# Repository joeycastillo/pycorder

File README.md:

The PyCorder
============

A credit-card-sized, SAM D51-based gadget for sensing, storing and showing data.

PCB (new link soon)) | [BOM](https://octopart.com/bom-tool/ggGZZjZ3) | [UPDATES](https://twitter.com/josecastillo)

Features
--------

* A distinctly crisp and impressively low power 240x400 Sharp Memory Display
* A SAMD51G19 microcontroller, with plenty of room for [CircuitPython](https://circuitpython.org/)!
* 4 megabyte QSPI Flash; plenty of space for code, fonts and images
* Two buttons and a five-way joystick for user input
* Built-in battery charging, and room for a [350 mAh battery](https://www.adafruit.com/product/4237)
* One STEMMA port with current limiting and voltage protection
* One STEMMA-QT port for plugging in [STEMMA-QT compatible boards](https://www.adafruit.com/category/1018)
* One 9-pin connector, compatible with a veritable menagerie of [Sensor Cap](https://github.com/joeycastillo/Sensor-Cap/tree/main/PCB/Sensor%20Boards) sensor boards
* Enable switch for cutting power to the device
* One amber LED for charge state and one red LED for general purpose blinking

Building your own PyCorder
--------------------------

You will need to order the PCB's from someplace like OSH Park (I recommend getting it in After Dark), and purchase all the parts on the [PyCorder Bill of Materials](https://octopart.com/bom-tool/ggGZZjZ3).

The board is hand-solderable, but a word of warning: **this is a relatively advanced build**. The SAM D51 microcontroller is a QFN part, which is best soldered with a hot air reflow station. Aside from that, almost all of the passive components are 0603 in size, which is at the limit of hand-solderability for many folks. A [fine tip](https://www.adafruit.com/product/1249) for your soldering iron is a must, and a [syringe of flux](https://www.adafruit.com/product/2667) couldn't hurt.

Pin definitions
---------------

Unlike a Metro or even a Feather, the PyCorder doesn't have a whole heap of GPIO pins. Having said that, I made sure to choose the pins with the most diverse set of features, opening the door to a whole lot of possibilities.

The **STEMMA port** is arguably one of the most powerful pins on the microcontroller. You can use it as a 10-bit true analog output, analog input, digital in/out or PWM. Access it in CircuitPython as `board.STEMMA`.

The **STEMMA-QT port** gives access to the board's I²C pins. Get at the I²C bus with `board.I2C()`, or the pins with `board.SDA` / `board.SCL`.

The **9-pin connector** can be used in a lot of different ways. From the top of the connector (which is pin 9):

* Pin 9, or `board.A0`, is the SAMD51's other DAC channel. Use this as an analog output, analog input or digital in/out.
* Pins 8 and 7 are the same I²C pins as the STEMMA-QT port; all I²C devices share the `board.I2C()` bus.
* Pin 6 has two names: `board.A1` and `board.SCK`. It can act as an analog input, PWM or digital in/out. In addition, it can act as the SCK pin for an SPI device on the other end of the 9-pin cable.
* Pin 5 (`board.A2` / `board.MOSI`) can act as an analog input, PWM, digital in/out, and the Main Out / Secondary In for an SPI device.
* Pin 4 (`board.D0` / `board.CS`) cannot support analog input, but you do get PWM and digital in/out. Can act as chip select for an SPI device.
* Pin 3 (`board.D1` / `board.MISO`) is PWM or digital in/out. Can act as the Main In / Secondary Out for an SPI device.
* Pin 2 is ground. 
* Pin 1 is a regulated 3.3 volt output from the on-board regulator.

The board has a **dual-output votage regulator** that can gate power to these three ports separately from the rest of the device. The enable pin for the main regulator output is, of course, tied to the on/off switch and pulled up by default. The second enable pin is tied to CircuitPython's `board.EN2`, and it is *pulled down by default*. This means that to power any device plugged in to these ports, you must do something like this first: 

```
en2 = DigitalInOut(board.EN2)
en2.switch_to_output()
en2.value = True
```

The LED is accessible at `board.LED`; you can output a digital signal to turn it on and off, or fade it with PWM.

Finally: the button inputs. These are easy: they're all active low and tied directly to pins on the SAMD51 (so you should enable internal pull-up resistors to use them). The rundown: 

* The button on the left side of the board is `board.PREVIOUS`
* The button on the right side is `board.NEXT`
* The four cardinal directions of the joystick map to `board.UP`, `board.DOWN`, `board.LEFT`, and `board.RIGHT`.
* You can press in on the joystick as a 'select' type action; detect this action on the `board.CENTER` pin.

Burning the bootloader
----------------------

You will burn the bootloader over the SWD interface. These pins are available as exposed test points on the right side of the back of the board. To connect to them, you can solder directly to the pads, or use pogo pins; they are 0.1 inch pitch, so you can make a compatible cable using [a 5x1 wire housing](https://www.adafruit.com/product/3145), [raw jumper wires](https://www.adafruit.com/product/3633) and [some pogo pins](https://www.adafruit.com/product/2429).

For convenience, a prebuilt bootloader is available in this repository. You can burn the bootloader using any SWD debugging tool like a J-Link or Atmel-ICE, but you can also use an [Adafruit Trinket M0](https://www.adafruit.com/product/3500) or [PyRuler](https://www.adafruit.com/product/4319) and the [Adafruit_DAP](https://github.com/adafruit/Adafruit_DAP) library.

You can also build the bootloader from scratch by copying the `bootloader/pycorder_m4` directory to the `boards` directory of [uf2-samdx1](https://github.com/adafruit/uf2-samdx1) and typing `make BOARD=pycorder_m4`.

CircuitPython on the PyCorder
-----------------------------

A CircuitPython UF2 is not included in this repository, because it's probably better to build your own with the latest greatest features. To get set up, follow the instructions in [Adafruit's guide to building CircuitPython](https://learn.adafruit.com/building-circuitpython?view=all); then copy the `circuitpython/pycorder_m4` directory to the CircuitPython repository's `ports/atmel-samd/boards` directory. 

Navigate to the `ports/atmel-samd` folder in your terminal and type `make BOARD=pycorder_m4`. This will generate a UF2 that you can drag to the PYCOBOOT drive.

Note that the CircuitPython build does not currently drive the display by default. Whether you intend to display console output or your own UI, you will have to paste some code like this at the beginning of your `code.py` to get the display working:

```
import busio
import framebufferio
import sharpdisplay
displayio.release_displays()
bus = busio.SPI(board.DISPLAY_CLOCK, MOSI=board.DISPLAY_DATA)
framebuffer = sharpdisplay.SharpMemoryFramebuffer(bus, board.DISPLAY_CS, 400, 240)
display = framebufferio.FramebufferDisplay(framebuffer, auto_refresh = True, rotation=270)
```

At this point you can add `display.show(None)` to display the CircuitPython console, or if you wish to show a displayio Group, `display.show(your_group)`.

Two final notes on the display: first, per the data sheet, the display requires a constant ~1Hz pulse on its EXTCOMIN pin. This reverses the polarity of the LCD, and is necessary for the display's long term stability. The CircuitPython board definition sets this pulse up as a PWM in its `board_init` function. If you wanted to do something like an Arduino core for it, you would be responsible for zatzing the display roughly once a second. EXTCOMIN is tied to the SAMD51's pin PA01, and the TC2 peripheral is ideal for generating this signal.

Second: the display only turns on when its DISP pin is pulled high, but the PyCorder connects it via a pull-down resistor so that the display defaults to an off state. This is intentional: the goal is to prevent the screen from turning on in the absence of the EXTCOMIN signal and degrading. DISP is tied to the SAMD51's pin PA00, and the `board_init` function pulls it high right after setting up the 1Hz pulse. This means that as long as the board is running, the screen will be on and the EXTCOMIN signal will be going to the screen.

Schematics and resources
------------------------

TODO

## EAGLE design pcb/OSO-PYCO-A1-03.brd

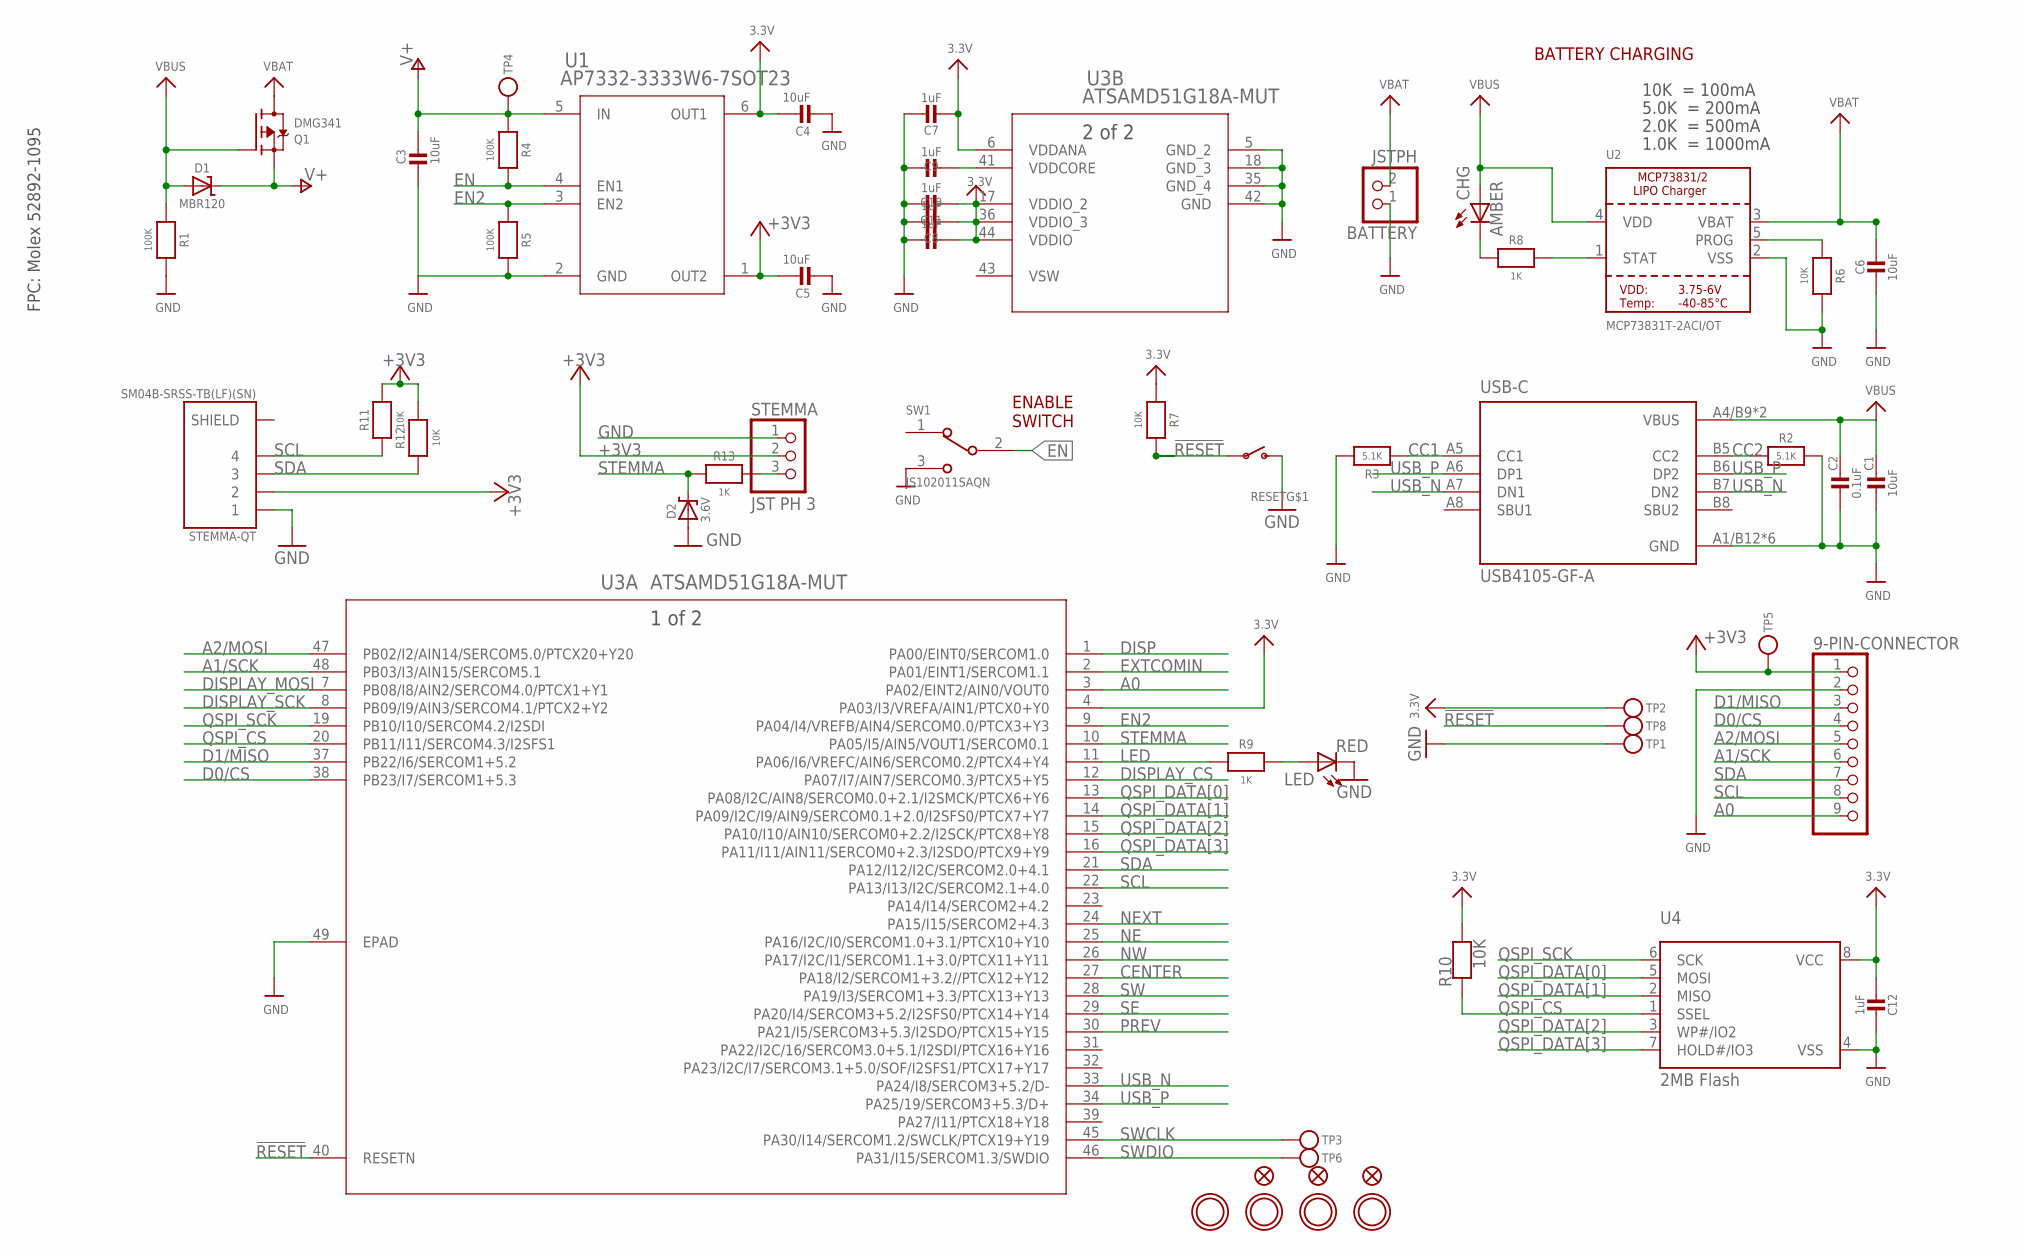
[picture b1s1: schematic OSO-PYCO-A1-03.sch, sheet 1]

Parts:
9-PIN-CONNECTOR: HEADER-1X9_JSTSH; JST_SH9
BATTERY: JSTPH; JSTPH2
C1, C3, C4, C5, C6: 10uF; 0805-NO
C2: 0.1uF; _0603MP
C7, C8, C9, C10, C11, C12: 1uF; _0603MP
CHG: AMBER; CHIP-LED0805
D1: MBR120; SOD-123
D2: 3.6V; SOD-123
FID1, FID2, FID3: FIDUCIAL_1MM
LED: RED; CHIP-LED0805
Q1: DMG341; SOT23-R
R1, R4, R5: 100K; _0603MP
R2, R3: 5.1K; _0603MP
R6, R7, R10, R11, R12: 10K; _0603MP
R8, R9, R13: 1K; _0603MP
RESET: SWITCH_SPSTTL3330A; TL3330A
STEMMA: JST PH 3; JSTPH3
STEMMA-QT: SM04B-SRSS-TB(LF)(SN); JST_SM04B-SRSS-TB(LF)(SN)
SW1: JS102011SAQN; SW_JS102011SAQN
TP1, TP2, TP3, TP4, TP5, TP6, TP8: TESTPOINTROUND2MMNO; TESTPOINT_ROUND_2MM_NO
U1: AP7332-3333W6-7SOT23; SOT23-6
U2: MCP73831T-2ACI/OT; SOT23-5
U3: ATSAMD51G18A-MUT; QFN48_7X7MC
U4: 2MB Flash; SOIC8_150MIL
U$9, U$10, U$27, U$28: MOUNTINGHOLE2.5; MOUNTINGHOLE_2.5_PLATED
USB-C: USB4105-GF-A; GCT_USB4105-GF-A

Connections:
3.3V: C4.1, C7.2, C8.2, C10.2, C11.2, C12.2, R7.1, R10.2, TP2.P$1, U1.6 (OUT1), U3.4 (PA03/I3/VREFA/AIN1/PTCX0+Y0), U3.6 (VDDANA), U3.17 (VDDIO_2), U3.36 (VDDIO_3), U3.44 (VDDIO), U4.8 (VCC); also elsewhere on the board
!RESET: R7.2, RESET.P$1, TP8.P$1, U3.40 (RESETN)
+3V3: 9-PIN-CONNECTOR.1, C5.1, R11.2, R12.2, STEMMA.2, STEMMA-QT.2, TP5.P$1, U1.1 (OUT2)
A0: 9-PIN-CONNECTOR.9, U3.3 (PA02/EINT2/AIN0/VOUT0)
A1/SCK: 9-PIN-CONNECTOR.6, U3.48 (PB03/I3/AIN15/SERCOM5.1)
A2/MOSI: 9-PIN-CONNECTOR.5, U3.47 (PB02/I2/AIN14/SERCOM5.0/PTCX20+Y20)
CC1: R3.1, USB-C.A5 (CC1)
CC2: R2.1, USB-C.B5 (CC2)
CENTER: U3.27 (PA18/I2/SERCOM1+3.2//PTCX12+Y12); also elsewhere on the board
D0/CS: 9-PIN-CONNECTOR.4, U3.38 (PB23/I7/SERCOM1+5.3)
D1/MISO: 9-PIN-CONNECTOR.3, U3.37 (PB22/I6/SERCOM1+5.2)
DISP: U3.1 (PA00/EINT0/SERCOM1.0); also elsewhere on the board
DISPLAY_CS: U3.12 (PA07/I7/AIN7/SERCOM0.3/PTCX5+Y5); also elsewhere on the board
DISPLAY_MOSI: U3.7 (PB08/I8/AIN2/SERCOM4.0/PTCX1+Y1); also elsewhere on the board
DISPLAY_SCK: U3.8 (PB09/I9/AIN3/SERCOM4.1/PTCX2+Y2); also elsewhere on the board
EN: R4.2, SW1.2, U1.4 (EN1); also elsewhere on the board
EN2: R5.1, U1.3 (EN2), U3.9 (PA04/I4/VREFB/AIN4/SERCOM0.0/PTCX3+Y3)
EXTCOMIN: U3.2 (PA01/EINT1/SERCOM1.1); also elsewhere on the board
GND: 9-PIN-CONNECTOR.2, BATTERY.1, C1.2, C2.2, C3.2, C4.2, C5.2, C6.2, C7.1, C8.1, C9.1, C10.1, C11.1, C12.1, D2.A, LED.C, R1.2, R2.2, R3.2, R5.2, R6.2, RESET.P$2 (S), STEMMA.1, STEMMA-QT.1, SW1.3, TP1.P$1, U1.2 (GND), U2.2 (VSS), U3.5 (GND_2), U3.18 (GND_3), U3.35 (GND_4), U3.42 (GND), U3.49 (EPAD), U4.4 (VSS), USB-C.A1/B12 (GND), USB-C.B1/A12 (GND), USB-C.G1 (GND), USB-C.G2 (GND), USB-C.G3 (GND), USB-C.G4 (GND); also elsewhere on the board
LED: R9.1, U3.11 (PA06/I6/VREFC/AIN6/SERCOM0.2/PTCX4+Y4)
unnamed: LED.A, R9.2
unnamed: CHG.C, R8.1
NE: U3.25 (PA16/I2C/I0/SERCOM1.0+3.1/PTCX10+Y10); also elsewhere on the board
NEXT: U3.24 (PA15/I15/SERCOM2+4.3); also elsewhere on the board
NW: U3.26 (PA17/I2C/I1/SERCOM1.1+3.0/PTCX11+Y11); also elsewhere on the board
PREV: U3.30 (PA21/I5/SERCOM3+5.3/I2SDO/PTCX15+Y15); also elsewhere on the board
PROG: R6.1, U2.5 (PROG)
QSPI_CS: R10.1, U3.20 (PB11/I11/SERCOM4.3/I2SFS1), U4.1 (SSEL)
QSPI_DATA[0]: U3.13 (PA08/I2C/AIN8/SERCOM0.0+2.1/I2SMCK/PTCX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), U4.5 (MOSI)
QSPI_DATA[1]: U3.14 (PA09/I2C/I9/AIN9/SERCOM0.1+2.0/I2SFS0/P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), U4.2 (MISO)
QSPI_DATA[2]: U3.15 (PA10/I10/AIN10/SERCOM0+2.2/I2SCK/PTCX8+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), U4.3 (WP#/IO2)
QSPI_DATA[3]: U3.16 (PA11/I11/AIN11/SERCOM0+2.3/I2SDO/PTCX9+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), U4.7 (HOLD#/IO3)
QSPI_SCK: U3.19 (PB10/I10/SERCOM4.2/I2SDI), U4.6 (SCK)
SCL: 9-PIN-CONNECTOR.8, R11.1, STEMMA-QT.4, U3.22 (PA13/I13/I2C/SERCOM2.1+4.0)
SDA: 9-PIN-CONNECTOR.7, R12.1, STEMMA-QT.3, U3.21 (PA12/I12/I2C/SERCOM2.0+4.1)
SE: U3.29 (PA20/I4/SERCOM3+5.2/I2SFS0/PTCX14+Y14); also elsewhere on the board
STAT: R8.2, U2.1 (STAT)
STEMMA: D2.C, R13.2, U3.10 (PA05/I5/AIN5/VOUT1/SERCOM0.1)
STEMMA_: R13.1, STEMMA.3
SW: U3.28 (PA19/I3/SERCOM1+3.3/PTCX13+Y13); also elsewhere on the board
SWCLK: TP3.P$1, U3.45 (PA30/I14/SERCOM1.2/SWCLK/PTCX19+Y19)
SWDIO: TP6.P$1, U3.46 (PA31/I15/SERCOM1.3/SWDIO)
USB_N: U3.33 (PA24/I8/SERCOM3+5.2/D-), USB-C.A7 (DN1), USB-C.B7 (DN2)
USB_P: U3.34 (PA25/19/SERCOM3+5.3/D+), USB-C.A6 (DP1), USB-C.B6 (DP2)
V+: C3.1, D1.C, Q1.2 (S), R4.1, TP4.P$1, U1.5 (IN); also elsewhere on the board
VBAT: BATTERY.2, C6.1, Q1.3 (D), U2.3 (VBAT)
VBUS: C1.1, C2.1, CHG.A, D1.A, Q1.1 (G), R1.1, U2.4 (VDD), USB-C.A4/B9 (VBUS), USB-C.B4/A9 (VBUS)
VDDCORE1: C9.2, U3.41 (VDDCORE)
VSW: U3.43 (VSW)

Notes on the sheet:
FPC: Molex 52892-1095
ENABLE SWITCH
10K = 100mA
5.0K = 200mA
2.0K = 500mA
1.0K = 1000mA
BATTERY CHARGING

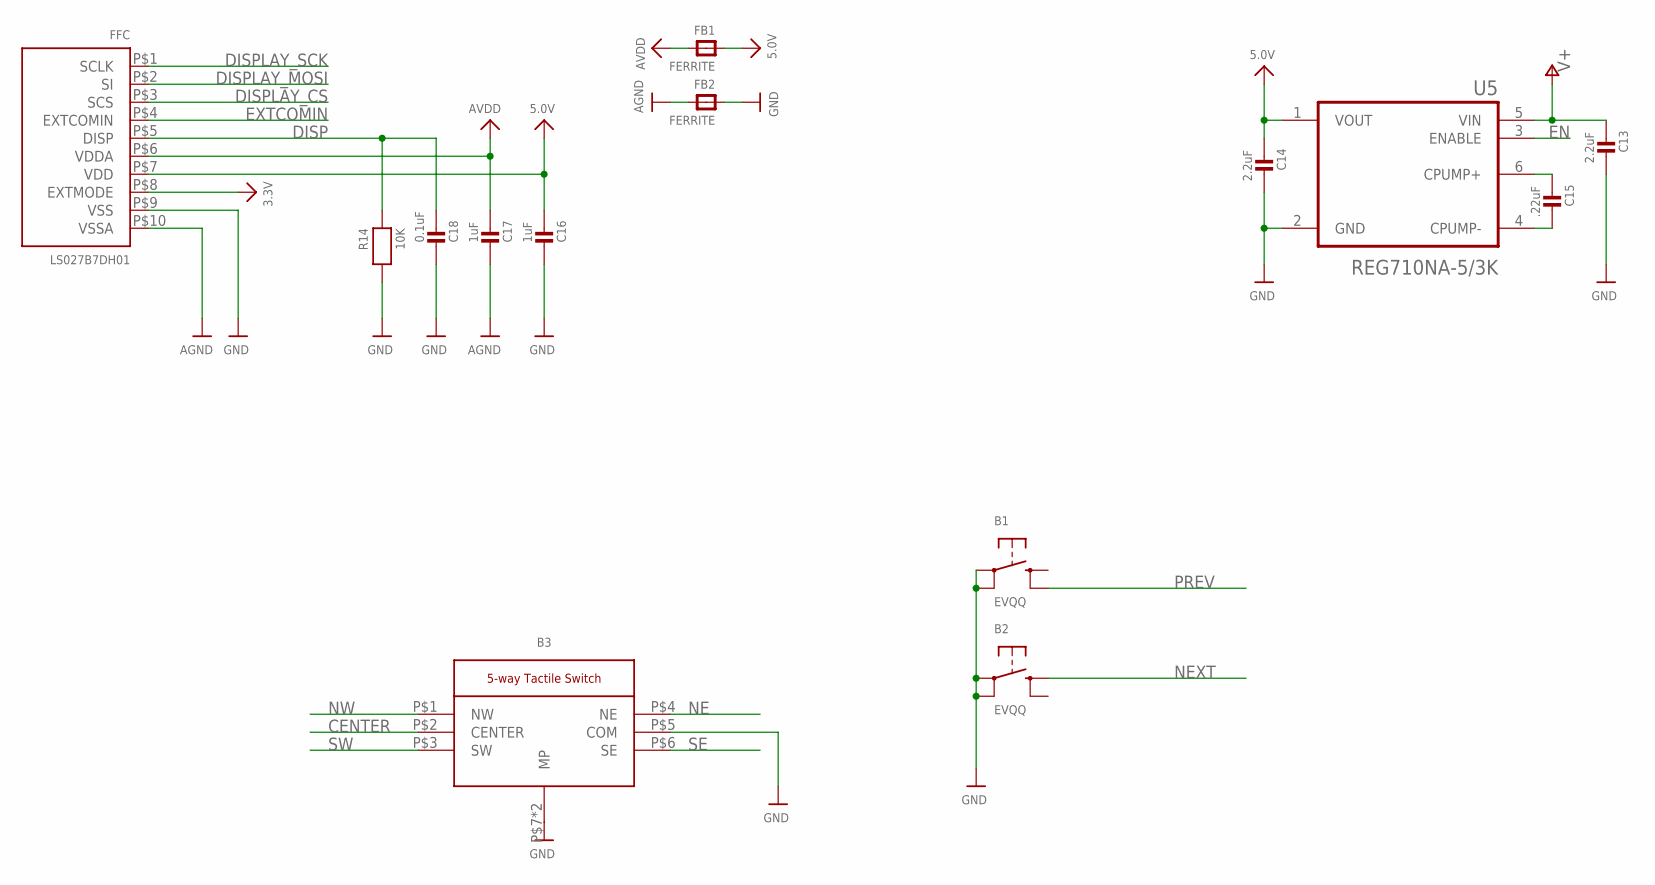
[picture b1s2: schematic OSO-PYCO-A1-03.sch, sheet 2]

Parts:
B1, B2: EVQQ; 6MMX6MM_TACTILE_SMT
B3: K1-5202UA
C13, C14: 2.2uF; _0603MP
C15: .22uF; _0603MP
C16, C17: 1uF; _0603MP
C18: 0.1uF; _0603MP
FB1, FB2: FERRITE; _0805
FFC: LS027B7DH01; SHARP_2.7IN
R14: 10K; _0603MP
U5: REG710NA-5/3K; SOT95P280X145-6N

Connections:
3.3V: FFC.P$8 (EXTMODE); also elsewhere on the board
5.0V: C14.1, C16.1, FB1.1, FFC.P$7 (VDD), U5.1 (VOUT)
AGND: C17.2, FB2.2, FFC.P$10 (VSSA)
AVDD: C17.1, FB1.2, FFC.P$6 (VDDA)
CENTER: B3.P$2 (CENTER); also elsewhere on the board
DISP: C18.1, FFC.P$5 (DISP), R14.1; also elsewhere on the board
DISPLAY_CS: FFC.P$3 (SCS); also elsewhere on the board
DISPLAY_MOSI: FFC.P$2 (SI); also elsewhere on the board
DISPLAY_SCK: FFC.P$1 (SCLK); also elsewhere on the board
EN: U5.3 (ENABLE); also elsewhere on the board
EXTCOMIN: FFC.P$4 (EXTCOMIN); also elsewhere on the board
GND: B1.A, B1.A' (P1), B2.A, B2.A' (P1), B3.P$5 (COM), B3.P$7 (MP), B3.P$8 (MP), C13.2, C14.2, C16.2, C18.2, FB2.1, FFC.P$9 (VSS), R14.2, U5.2 (GND); also elsewhere on the board
unnamed: C15.1, U5.6 (CPUMP+)
unnamed: C15.2, U5.4 (CPUMP-)
NE: B3.P$4 (NE); also elsewhere on the board
NEXT: B2.B (S); also elsewhere on the board
NW: B3.P$1 (NW); also elsewhere on the board
PREV: B1.B' (S1); also elsewhere on the board
SE: B3.P$6 (SE); also elsewhere on the board
SW: B3.P$3 (SW); also elsewhere on the board
V+: C13.1, U5.5 (VIN); also elsewhere on the board

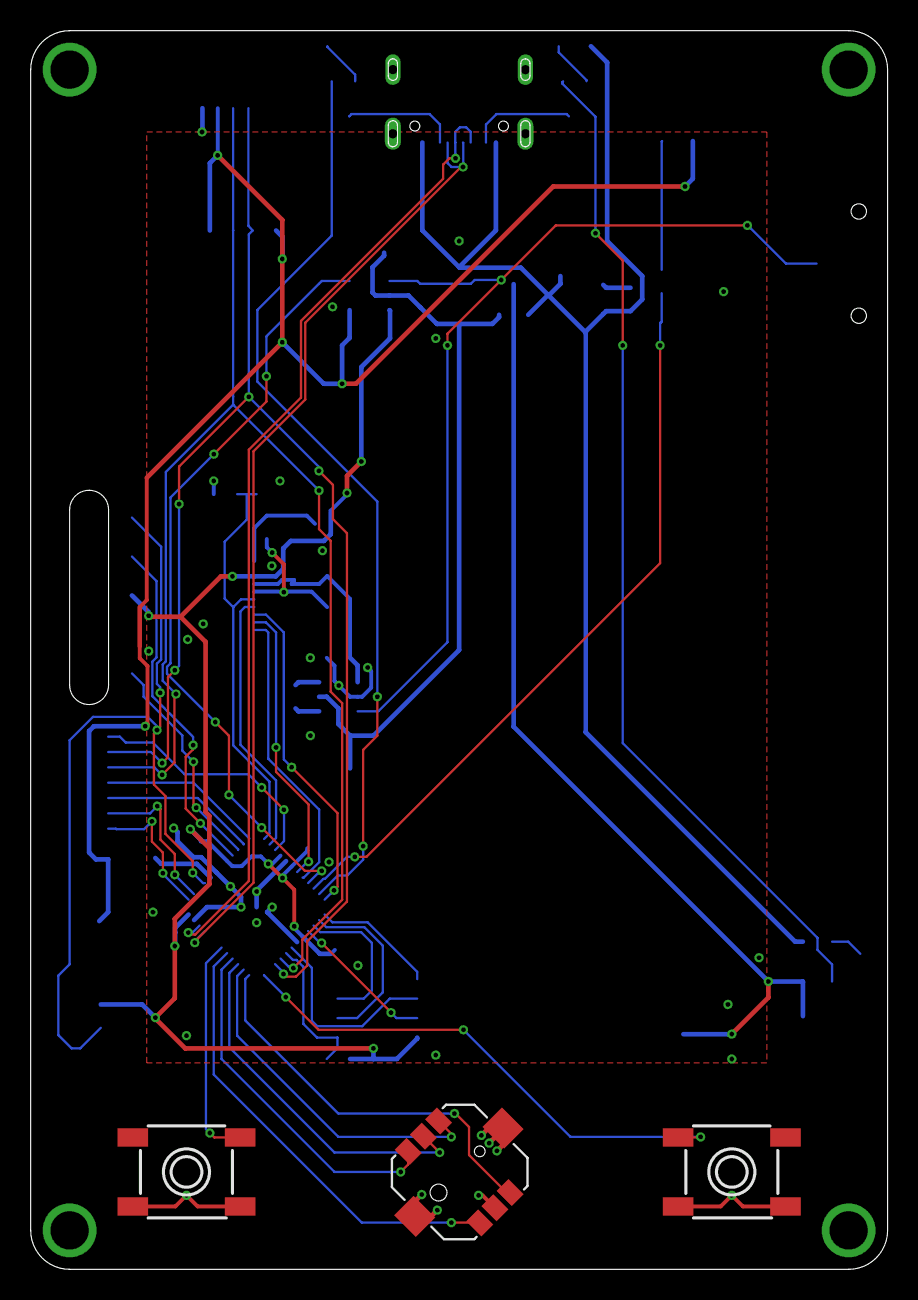
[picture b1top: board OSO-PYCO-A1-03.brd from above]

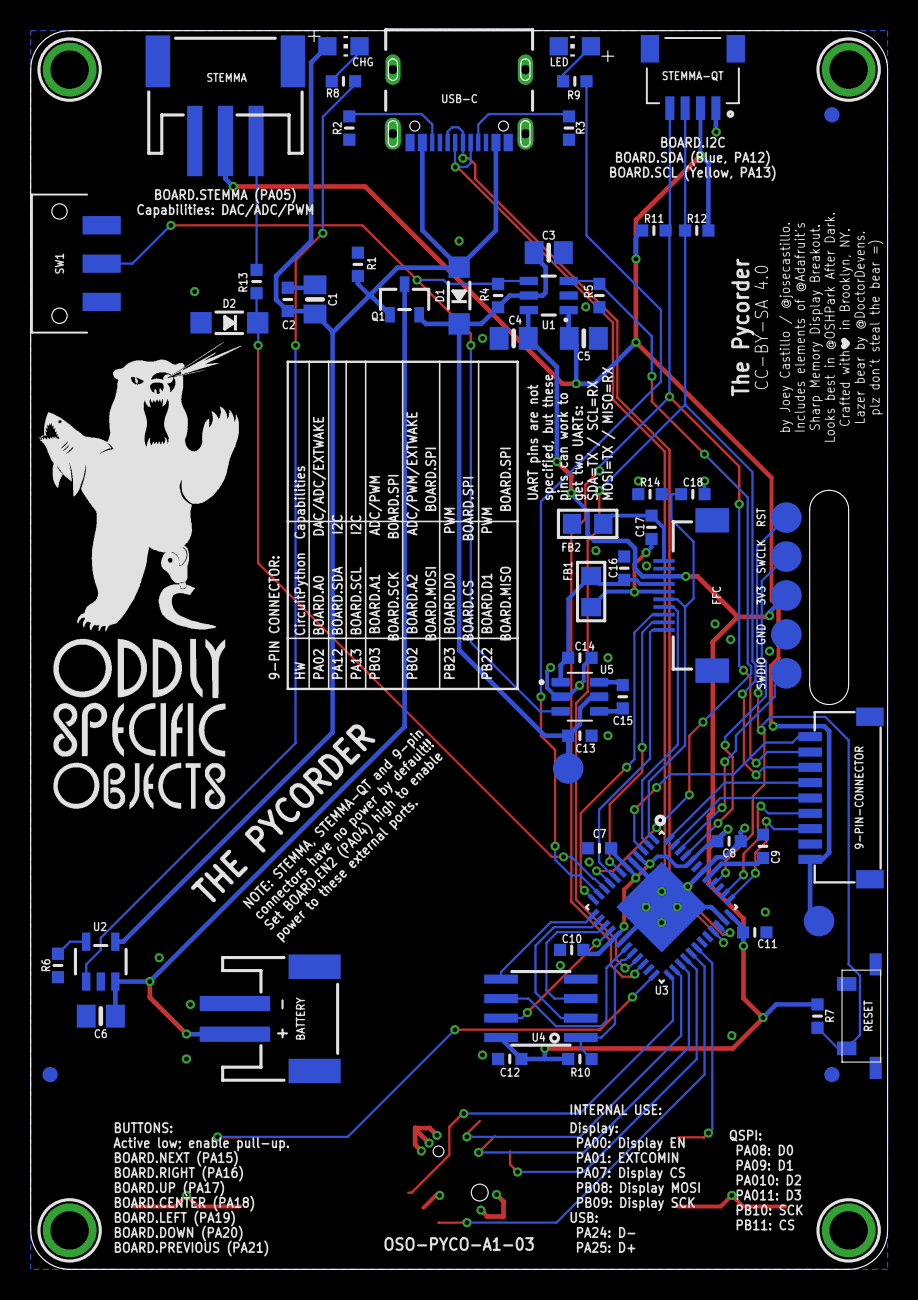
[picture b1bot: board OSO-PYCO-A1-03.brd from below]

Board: 2 copper layers, 55.9 x 80.8 mm, 71 parts (68 on the bottom side), 53 nets.

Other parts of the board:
U$16: OSO_WORDMARK_THREELINE_450MIL_1000DPI
U$67: OSO_BEAR_525X750MIL_1000DPI

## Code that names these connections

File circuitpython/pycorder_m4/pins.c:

#include "shared-bindings/board/__init__.h"

STATIC const mp_rom_map_elem_t board_global_dict_table[] = {
    { MP_OBJ_NEW_QSTR(MP_QSTR_A0), MP_ROM_PTR(&pin_PA02) },
    { MP_OBJ_NEW_QSTR(MP_QSTR_A1), MP_ROM_PTR(&pin_PB03) },
    { MP_OBJ_NEW_QSTR(MP_QSTR_SCK), MP_ROM_PTR(&pin_PB03) },
    { MP_OBJ_NEW_QSTR(MP_QSTR_A2), MP_ROM_PTR(&pin_PB02) },
    { MP_OBJ_NEW_QSTR(MP_QSTR_MOSI), MP_ROM_PTR(&pin_PB02) },
    { MP_OBJ_NEW_QSTR(MP_QSTR_D0), MP_ROM_PTR(&pin_PB23) },
    { MP_OBJ_NEW_QSTR(MP_QSTR_CS), MP_ROM_PTR(&pin_PB23) },
    { MP_OBJ_NEW_QSTR(MP_QSTR_D1), MP_ROM_PTR(&pin_PB22) },
    { MP_OBJ_NEW_QSTR(MP_QSTR_MISO), MP_ROM_PTR(&pin_PB22) },

    { MP_OBJ_NEW_QSTR(MP_QSTR_STEMMA), MP_ROM_PTR(&pin_PA05) },

    { MP_OBJ_NEW_QSTR(MP_QSTR_LED), MP_ROM_PTR(&pin_PA06) },
    { MP_OBJ_NEW_QSTR(MP_QSTR_EN2), MP_ROM_PTR(&pin_PA04) },

    { MP_OBJ_NEW_QSTR(MP_QSTR_SDA),MP_ROM_PTR(&pin_PA12) },
    { MP_OBJ_NEW_QSTR(MP_QSTR_SCL),MP_ROM_PTR(&pin_PA13) },

    { MP_OBJ_NEW_QSTR(MP_QSTR_DISPLAY_DATA),MP_ROM_PTR(&pin_PB08) },
    { MP_OBJ_NEW_QSTR(MP_QSTR_DISPLAY_CLOCK),MP_ROM_PTR(&pin_PB09) },
    { MP_OBJ_NEW_QSTR(MP_QSTR_DISPLAY_CS),MP_ROM_PTR(&pin_PA07) },

    { MP_OBJ_NEW_QSTR(MP_QSTR_UP),MP_ROM_PTR(&pin_PA17) },
    { MP_OBJ_NEW_QSTR(MP_QSTR_RIGHT),MP_ROM_PTR(&pin_PA16) },
    { MP_OBJ_NEW_QSTR(MP_QSTR_DOWN),MP_ROM_PTR(&pin_PA20) },
    { MP_OBJ_NEW_QSTR(MP_QSTR_LEFT),MP_ROM_PTR(&pin_PA19) },
    { MP_OBJ_NEW_QSTR(MP_QSTR_CENTER),MP_ROM_PTR(&pin_PA18) },
    { MP_OBJ_NEW_QSTR(MP_QSTR_NEXT),MP_ROM_PTR(&pin_PA15) },
    { MP_OBJ_NEW_QSTR(MP_QSTR_PREVIOUS),MP_ROM_PTR(&pin_PA21) },

    { MP_ROM_QSTR(MP_QSTR_I2C), MP_ROM_PTR(&board_i2c_obj) },
    { MP_ROM_QSTR(MP_QSTR_SPI), MP_ROM_PTR(&board_spi_obj) },
    { MP_ROM_QSTR(MP_QSTR_UART), MP_ROM_PTR(&board_uart_obj) },
};

MP_DEFINE_CONST_DICT(board_module_globals, board_global_dict_table);

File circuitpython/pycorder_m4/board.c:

#include "supervisor/board.h"
#include "mpconfigboard.h"
#include "shared-bindings/pwmio/PWMOut.h"
#include "hal/include/hal_gpio.h"

void board_init(void) {
    // set up square wave on PA01 (display EXTCOMIN)
    pwmio_pwmout_obj_t pwm;
    common_hal_pwmio_pwmout_construct(&pwm, &pin_PA01, 32768, 2, false);
    common_hal_pwmio_pwmout_never_reset(&pwm);

    // keep display on at all times (display DISP is PA00)
    gpio_set_pin_function(PIN_PA00, GPIO_PIN_FUNCTION_OFF);
    gpio_set_pin_direction(PIN_PA00, GPIO_DIRECTION_OUT);
    gpio_set_pin_level(PIN_PA00, true);
    never_reset_pin_number(PIN_PA00);
}

bool board_requests_safe_mode(void) {
    return false;
}

void reset_board(void) {
}

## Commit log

2021-03-20 typo fixes, add some links
2022-06-17 pycorder rev 3

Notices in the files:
pcb/OSO-PYCO-A1-03.brd:
CC-BY-SA 4.0
parts and their libraries:
COPYRIGHT: Copyright (C) 2018 Accelerated Designs. All rights reserved
